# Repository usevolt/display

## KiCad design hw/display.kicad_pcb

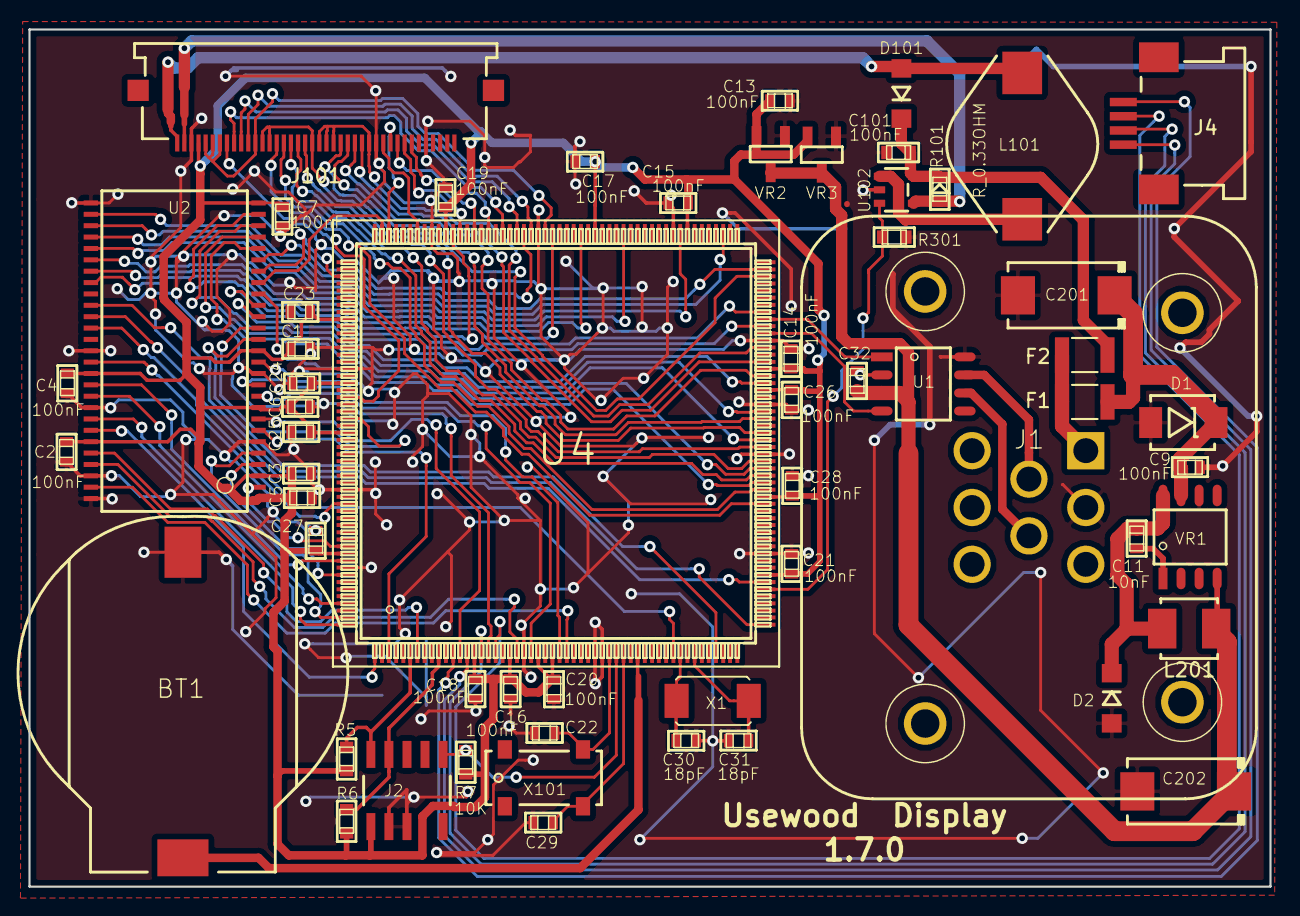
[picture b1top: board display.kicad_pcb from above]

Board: 2 copper layers, 87.3 x 60.3 mm, 58 parts (0 on the bottom side), 87 nets.

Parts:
BT1: BATTERY_HOLDER_CH7410-2032LFSMD; usevolt-BATTERY_HOLDER_CH7410-2032LF
C1, C2, C3, C4, C5, C6, C7, C9, C13, C14, C15, C16, C17, C18, C19, C20, C21, C23, C24, C25, C26, C27, C28, C32: 100nF; Kemet-CAPC1608X85N
C11: 10nF; Kemet-CAPC1608X85N
C22, C29: 12pF; Kemet-CAPC1608X85N
C30, C31: 18pF; Kemet-CAPC1608X85N
C101: 100nF; 0603
C201, C202: T491D226K035AT; 7343
D1: DIODE_TVS_SMBJ33A-TRDO-214AA; DO-214AA
D2, D101: DIODE_RS07J-GS18; DO219AB
F1, F2: FUSE_0ZCH0075AF2E; 1210
J1: AMPSEAL_8_POS_776275-1
J2: ARM_JTAG_SWD_HEADER_10_PINSMD; usevolt-ARM_10_PIN_JTAG_SWD_CONNECTOR
J4: HEADER_MOLEX_52207-0433
J101: HEADER_MOLEX_54104-4031
L101: INDUCTOR_SDR1005-101KL; INDUCTOR_BOURNS_10X13X5MM
L201: IND_744045210
R5, R6, R7: 10K; Multicomp-RESC1608X60N
R101: R_0.33OHM; 0603
R301: 10K; 0603
U1: MCP2551_SOIC8; SOIC8
U2: ALLIANCE_AS4C4M16SA_TSOP_II; TSOP_II_54_PIN
U4: LPC1785FBD208_551QFP50; QFP208
U102: AL8805W5-7_LED_DRIVER; SOT-25
VR1: LM2671SOIC8; SOIC8
VR2, VR3: REG_MCP1700; SOT-23_3-PIN
X1: XTAL_7A-20.000MAAJ-T; XTAL_7A-20.000MAJ
X101: XTAL_ABS25-32.768KHZ-T; XTAL_32.768KHZ-T

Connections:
+3V3: C1.1, C2.1, C3.2, C4.2, C5.2, C6.2, C7.2, C13.1, C14.1, C15.1, C16.1, C17.1, C18.1, C19.1, C20.1, C21.1, C23.1, C24.1, C25.1, C26.1, C27.1, C28.1, J2.P$1, J101.4, R5.2, R6.2, R7.2, U2.P$1, U2.P$3, U2.P$9, U2.P$14, U2.P$27, U2.P$43, U2.P$49, U4.15, U4.20, U4.24, U4.26, U4.60, U4.71, U4.86, U4.89, U4.112, U4.125, U4.146, U4.165, U4.174, U4.181, U4.198, VR2.2, VR3.2
+5V: C32.1, C202.+, L201.2, U1.P$3, VR1.P$4, VR2.3, VR3.3
/A0: U2.P$23, U4.75
/A1: U2.P$24, U4.79
/A2: U2.P$25, U4.83
/A3: U2.P$26, U4.97
/A4: U2.P$29, U4.103
/A5: U2.P$30, U4.107
/A6: U2.P$31, U4.113
/A7: U2.P$32, U4.121
/A8: U2.P$33, U4.127
/A9: U2.P$34, U4.131
/A10: U2.P$22, U4.135
/A11: U2.P$35, U4.145
/B0: J101.24, U4.102
/B1: J101.25, U4.82
/B2: J101.26, U4.88
/B3: J101.27, U4.90
/B4: J101.21, J101.22, J101.23, J101.28, U4.92
/BA0: U2.P$20, U4.155
/BA1: U2.P$21, U4.159
/BACKLIGHT: R301.2, U4.58, U102.3
/BCKL+: J101.2, R101.2, U102.4
/BCKL-: D101.P$1, J101.1, L101.P$2
/CANH: J1.P$4, U1.P$7
/CANL: J1.P$5, U1.P$6
/DCLK: J101.30, U4.150
/DE: J101.34, U4.142
/DQ0: U2.P$2, U4.197
/DQ1: U2.P$4, U4.201
/DQ2: U2.P$5, U4.207
/DQ3: U2.P$7, U4.3
/DQ4: U2.P$8, U4.13
/DQ5: U2.P$10, U4.17
/DQ6: U2.P$11, U4.23
/DQ7: U2.P$13, U4.27
/DQ8: U2.P$42, U4.191
/DQ9: U2.P$44, U4.199
/DQ10: U2.P$45, U4.205
/DQ11: U2.P$47, U4.208
/DQ12: U2.P$48, U4.1
/DQ13: U2.P$50, U4.7
/DQ14: U2.P$51, U4.21
/DQ15: U2.P$53, U4.28
/G0: J101.15, U4.70
/G1: J101.16, U4.72
/G2: J101.17, U4.74
/G3: J101.18, U4.76
/G4: J101.19, U4.78
/G5: J101.13, J101.14, J101.20, U4.80
/HSYNC: J101.32, U4.140
/PWR: J101.31, U4.154
/R0: J101.8, U4.176
/R1: J101.9, U4.138
/R2: J101.10, U4.136
/R3: J101.11, U4.134
/R4: J101.5, J101.6, J101.7, J101.12, U4.132
/VSYNC: J101.33, U4.144
/lpc1785_sheet/CAN_RXD: U1.P$4, U4.94
/lpc1785_sheet/CAN_TXD: U1.P$1, U4.96
/lpc1785_sheet/EMC_CAS: U2.P$17, U4.87
/lpc1785_sheet/EMC_CKE: U2.P$37, U4.53
/lpc1785_sheet/EMC_CLK: U2.P$38, U4.59
/lpc1785_sheet/EMC_CS: U2.P$19, U4.73
/lpc1785_sheet/EMC_DQM0: U2.P$15, U4.49
/lpc1785_sheet/EMC_DQM1: U2.P$39, U4.43
/lpc1785_sheet/EMC_RAS: U2.P$18, U4.95
/lpc1785_sheet/EMC_WE: U2.P$16, U4.179
/lpc1785_sheet/LCD_X_L: J4.1, U4.14
/lpc1785_sheet/LCD_X_R: J4.3, U4.18
/lpc1785_sheet/LCD_Y_B: J4.2, U4.16
/lpc1785_sheet/LCD_Y_T: J4.4, U4.12
/lpc1785_sheet/RESET: J2.P$9, R7.1, U4.35
/lpc1785_sheet/RTC_BAT: BT1.+, U4.38
/lpc1785_sheet/RTC_X1: C22.2, U4.34, X101.1
/lpc1785_sheet/RTC_X2: C29.2, U4.36, X101.4
/lpc1785_sheet/SWDCLK: J2.P$4, R6.1, U4.10
/lpc1785_sheet/SWDIO: J2.P$2, R5.1, U4.6
/pwr_supply_sheet/VIN: F1.1, F2.1, J1.P$1
/pwr_supply_sheet/VLCD: C101.2, D101.P$2, F2.2, R101.1, U102.5
GND: BT1.-, C1.2, C2.2, C3.1, C4.1, C5.1, C6.1, C7.1, C9.2, C13.2, C14.2, C15.2, C16.2, C17.2, C18.2, C19.2, C20.2, C21.2, C22.1, C23.2, C24.2, C25.2, C26.2, C27.2, C28.2, C29.1, C30.1, C31.1, C32.2, C101.1, C201.-, C202.-, D1.P$1, D2.P$1, J1.P$2, J2.P$3, J2.P$5, J101.3, J101.29, J101.36, R301.1, U1.P$2, U1.P$8, U2.P$6, U2.P$12, U2.P$28, U2.P$41, U2.P$46, U2.P$52, U2.P$54, U4.22, U4.32, U4.33, U4.63, U4.77, U4.84, U4.93, U4.114, U4.133, U4.148, U4.169, U4.172, U4.189, U4.200, U102.2, VR1.P$6, VR2.1, VR3.1
unnamed: C11.1, VR1.P$1
unnamed: C11.2, D2.P$2, L201.1, VR1.P$8
unnamed: C30.2, U4.44, X1.P$1
unnamed: C31.2, U4.46, X1.P$2
unnamed: L101.P$1, U102.1
VDD: C9.1, C201.+, D1.P$2, F1.2, VR1.P$7

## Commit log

2016-02-07 Add initial HW files
    - HW files includes version 1.0 & 1.1 eagle files
2016-02-23 Move doc directory from hw to root
2016-03-17 Start developing the display SW
    - Testing freertos
    - UART, timers and gpios are working
    - Add uGUI library to ui directory
2016-04-05 Display runs now with uw_bootloader
2016-04-05 HAL library is linked via git submodule
2016-04-30 Creating interface for external memory
2016-07-04 implementing the EMC interface, not ready yet
2016-07-04 HAL library changed from uw to uv
2016-08-15 Corrected HW connector bolt sizes
2016-08-15 back enclosure bolt hole sizes reduced
2016-09-01 revision 2 pcb ordered from itead
2016-09-07 PCB was too big for itead, reduced size and ordered one
2016-09-12 testing with hard fault
2016-10-02 windows and texts working in UI
2016-10-02 Changed LCD interface from RGB888 to RGB565
2016-10-17 HW revision 3 ordered from itead
2016-10-24 Project changed to use Usevolt makefile
2016-10-28 building the UI: brightness and volume sliders in settings
2016-10-28 release -build-directory excluded from the repository
2016-10-30 oil & fuel level, temperature bars added to taskbar
2016-10-31 Version 4 ordered from shapeways
2016-11-22 can implementing...
2016-12-25 uw180s & uw50 setting pages created
2016-12-31 Almost working version
2017-01-02 first working version
2017-01-04 HAL submodule uses usevolt server as remote
2017-01-04 Removed UI library from project as useless
2017-01-10 snapping connectors for front enclosure
2017-01-20 creating logging interface. Not tested
2017-01-23 Implementing notifications. not tested!
2017-02-01 back encolosure tightning
2017-02-01 enclosure front screw holes widened
2017-02-01 enclosure front screw holes deepened
2017-02-04 working log interface
2017-02-07 heater implemented
2017-02-07 system default values updated
2017-02-17 added snapping interfaces to enclosure
2017-02-17 Created builds for FM and LM
2017-02-22 multiple bug fixes, uv terminal SDO interface
2017-02-22 Rewriting CANopen hal module for improved portability
2017-02-24 small and simple log length variation added
2017-03-13 updated to uv_hal canopen v2
2017-03-13 emergency button implemented
2017-03-14 volume slider removed
2017-03-16 added engine light, emcy stop, LM implementations
2017-03-20 Reading gear from ECU TXPDO 3
2017-03-29 rpm & hydr pressure made global
2017-03-29 merging to old keypads
2017-04-03 uiwindow scrollbar testing
2017-04-04 keypad calibration implemnted, not tested
2017-04-12 corrected keypad calibration bugs
2017-04-12 LM build: Default implement set to UW100, drive back valve removed
2017-04-14 starting to design hw 5.0, with variable current source for LCD backlight
2017-04-16 implementing treeview for settings. Not ready!
2017-04-18 still implementing treeview, not ready
2017-04-18 LM_6.0.1 mods:
    heater canopen messages adjusted
    drive front speeds multiplied by 2
    gui backlight points inreased dramatically
2017-04-20 implementing uitreeview
2017-04-30 hw 1.5.0 ordered
2017-05-06 implementing uitreeview for general setting
2017-05-12 fm build updated to stepless ui init functions
2017-05-14 LM build for std driving valves (2 x LUDV)
2017-05-21 crp removed
2017-05-21 FM drive speed parameters multiplied by 2
2017-05-21 style fix: Unnecessary #if removed
2017-05-21 FM wheels feed max speed multiplied by 2
2017-05-24 settings general tab works again
2017-06-02 Combi Master build added
2017-06-03 CM modifications to alve names etc
2017-06-25 version control bug: pwr_supply_sheet now has fuse for LCD as in hw 1.5.0
2017-06-25 hw version 1.6.0
    * LCD backlight remains off while booting
    * BUZZER amplifying MOSFET circuit changed to low side driving
2017-06-27 small modifications to schematic
2017-07-04 decided to rewrite uitreeview so that uitreeobjects are the dynamic elements
2017-07-07 driving when legs down trigger warning
2017-07-07 valve default parameters adjusted
2017-07-07 default lcd brightness set to 80%
2017-07-07 boom lift, fold, uw180s saw, rotator default speeds adjusted
2017-07-09 bug fix: UW180s log len updated to ECU automatically
2017-07-12 bash script for taking screenshots created
2017-07-18 base machine valves, general settings & system diagnostics changed to uitreeview based
2017-07-18 new orange background colouring adjusted
2017-07-18 bug fix: cm & lm taskbar buffer was too short
2017-07-19 enclosure2 ready to order from shapeways
2017-08-07 hoil tempwarning limit increased to 85 c
2017-08-09 oil temperature warning increased to 80 c
2017-08-12 uw50 saw max speed multiplied by 2 in network: ecu.c
2017-08-20 hour calculator changed to minute counting
2017-08-30 msb heater as in old (0-2 speed)
2017-10-01 enclosure2 ampseal p pocket bugfix
2017-10-24 manual layout improved
2017-10-28 system network tab has data for FSB, ESB & CSB
2017-11-03 working revision with FSB, CSB & ESB
2017-11-15 implementing a multilinguality
2017-11-16 porting uv0a_hds pcb to uw_display
2017-11-20 1.7.0 pcb created, not yet ordered
2017-11-22 old enclosure files removed
2017-11-27 uw180s grab times adjustable
2017-12-10 default engine power usage set to 36
2017-12-19 hw 2.1.0 with LPC1549 & FT812 ordered from seeed
2017-12-19 2.1.0 schematic updates committed
2017-12-23 stencil gerber fixed (solder mask layer changed to solder paste layer
2018-01-23 unknown modifications to hw
2018-01-26 260117 Iceland: adding new users work, can error frames decreased
2018-01-26 valve default parameters set to fit LM_6.1.2
2018-01-27 unnecessary disconnected-warnings removed
2018-01-30 enclosure2_back bug fies
2018-02-05 FM_6.6.1 working revisioN
2018-02-16 uw180s mb min & max calibration buttons added
2018-02-24 heater & wiper moved to taskbar
2018-02-26 FM_6.4.1 new display sent 260218
2018-03-04 hour counter duplexed with ESB
2018-03-12 heater and wiper in taskbar, mb volume measurement working
2018-03-26 csb wiper request implemented
2018-03-28 ergo (fm_6.6.2) bug fix: display couts hours correctly.
2018-03-28 hour counter 32 bit value
2018-04-02 multilingual english & finnish implemented
2018-04-02 wiper logic reverted to previos version: display sets the wiper speed directly
2018-04-07 bug fixes when moving engine power usage to esb
2018-04-14 FM_6.5.1: uw180s mb nodeid 0xF
2018-04-19 kicad schematic update
2018-04-19 190418: disconnected and can bus alerts removed
2018-04-20 volume and width removed from uw180s dashboard
2018-05-04 040518: oil cooler trigger temp is remembered
2018-05-04 oilcooler trigger temp added to user data
2018-05-04 040518: oil cooler trigger temp is saved in display
2018-05-06 050518: icu interface for kikepera proto head
2018-05-29 working rtc module for LPC1549
2018-06-03 gerber files added to zip archive
2018-06-04 030618: seat switch implemented in ecu
2018-06-05 width measurement enabled, dirve max speed multiplied by 2
2018-06-06 060618: first working portotype, ready for testing in forest
2018-06-09 motor temp warning limit increased to 96 deg
2018-06-27 blades & rollers grab time settings added
2018-07-12 120718: kikepera harvester head widtha dn volume measurement
2018-08-14 log warnings disabled, motor temp warning increased
2018-08-15 140818: ESB, FSB, CSB added, display and ECU unmodofied
2018-08-29 compiles without lpcxpresso
2018-09-01 cr_section _macros removed
2018-09-01 asdasd
2018-09-01 010918: ads
2018-09-02 trying to get working with licr
2018-09-02 020918: added oilcooler trigget temp value
2018-09-09 CM_6.2.1 delivered, first customer machine with CCU, HCU & ICU
2018-09-13 network update disable implemented
2018-09-13 hal updated
2018-09-14 130918: working with kubota 1505T
2018-09-18 bugfixes in valve assembly invert settings
2018-10-14 141018: trying to build project withouth external linkage to NXP libraries
2018-10-14 141018: now compiles
2018-10-14 code red libraries added to hal display_master branch
2018-11-02 rollers grab time bugfix
2018-11-05 bugfix: ccu drive 2&3 speeds can be read in system network
2018-11-13 CM_6.2.1 released
2019-01-02 valve default currents modified to aaply with real currents
2019-01-21 deleted old lcd panel datasheet
2019-02-09 weird modifications
2019-02-10 pressing heater from taskbar toggles between on/off
2019-02-19 implementing user copy button, not yet tested
2019-02-25 tilt float added to uw180s settings
2019-03-16 uw180s tilt valve conf step decreased
2019-03-25 driving compensation added
2019-06-03 back steering implemented
2019-07-29 hydrout implement added
2019-07-29 bugfix: hydout valve settings are updated when implement is changed
2019-08-10 brightness req added to canopen interface
2019-08-22 version control changed to github
2019-08-23 impl2 valve is usable with uw100, usaful with skidding grapple
2019-10-09 submodule urls set to https github
2019-10-30 uw180s length target can be changed with right but3
2019-11-15 German translation replaced with swedish translations
2019-11-17 bugfix: drive compensation unsigned values changed to signed
2019-11-19 UW180s: tilt on thumb setting added
2019-11-29 swedish manual created
2019-12-14 radiator enable togglebutton added
2019-12-15 131219: radiator disable button added, valve default min values adjusted
2019-12-22 uw180s width measurement made easier: only min_mm and max_mm are required
2019-12-30 implementing tcu
2019-12-30 uw180s manual translations send
2020-01-02 TCU ready for first prototype tests
2020-01-02 020120: TCU interface implemented but reverted back old uw180s width calib
2020-01-02 021220: TCU telescope buttons revmoed
2020-01-02 TCU telescope buttons removed, controlled by lkeyboard
2020-01-17 ui glitch fix with kubota lights in taskbar
2020-01-18 taskbar hours ui glitch fix
2020-02-01 bugfixes: params are saved accross the network when operator changes, ccu telescope and backsteer params are udpated on op change only if they are enabled
2020-02-01 op change save parameters _after_ setting the params
2020-02-08 estonian manual added
2020-02-12 factory reset removed from boot up if display was pressed
2020-03-22 complies
2020-05-17 impl1 & impl2 are updated when changing to uw180s
2020-05-17 also rotator valve is updated when changing the implemen
2020-05-18 blades grab time removed from ui as deprecated
2020-05-19 icu uploads correct log length on start up
2020-05-19 updateing
2020-05-19 190520: updated drive compensation and faster display
2020-05-19 taskbar engine ligths glitch fix
2020-07-07 CCU AIN1&2 IMPL2 control implemented
2020-07-20 MTEMP warning limit increased to 105 deg
2020-07-20 enclosure files moved to enclosre directionry
2020-07-20 enclosure directory moved to root
2020-07-20 displa pcb reverted back to 1.6.0 revision and imporved to 1.7.0
2020-08-04 040820: drive back valve settings added
2020-08-04 040820: sensors are once again working
2020-08-05 mtemp bar limit is set only if water temp sensor triggers
2020-08-21 valve default speeds modified
2020-08-21 tilt on left thumb button removed
2020-08-21 add_user button removed from login
2020-09-05 converting mb nodeid back to default 0xD
2020-09-05 050920: mb nodeid set to default 0xD
2020-10-28 fsb heater speed renewed with cold air
2020-10-28 swedish translations updated according to Anders
2020-12-28 work rpm req implemented for stage5 engine
2020-12-30 heater speed color update
2021-01-04 stage 4 kubota version
2021-03-13 network bugfix
2021-04-09 display.json added
2021-06-04 taskbar heater speed bugfix
2022-06-28 drivedirection shown on gear
2024-04-08 tomi kuusisto alertsa removed from taskbar, double buffering disabled
2024-08-05 240805: alerts really removed, temp sensor scales increased
2025-12-10 j1939 force regen button added
